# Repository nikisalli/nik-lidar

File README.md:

# nik-lidar
a low cost 3d printed 3d lidar based on ydlidar-x4, esp32 and cheap parts!

- project status: complete, needs cleanup

# info
In this repo you can find all what's necessary to assemble your own 3d lidar able to make acceptable quality 360° 3d scans

feel free to contribute since I don't have time to clean up this project

# images and results

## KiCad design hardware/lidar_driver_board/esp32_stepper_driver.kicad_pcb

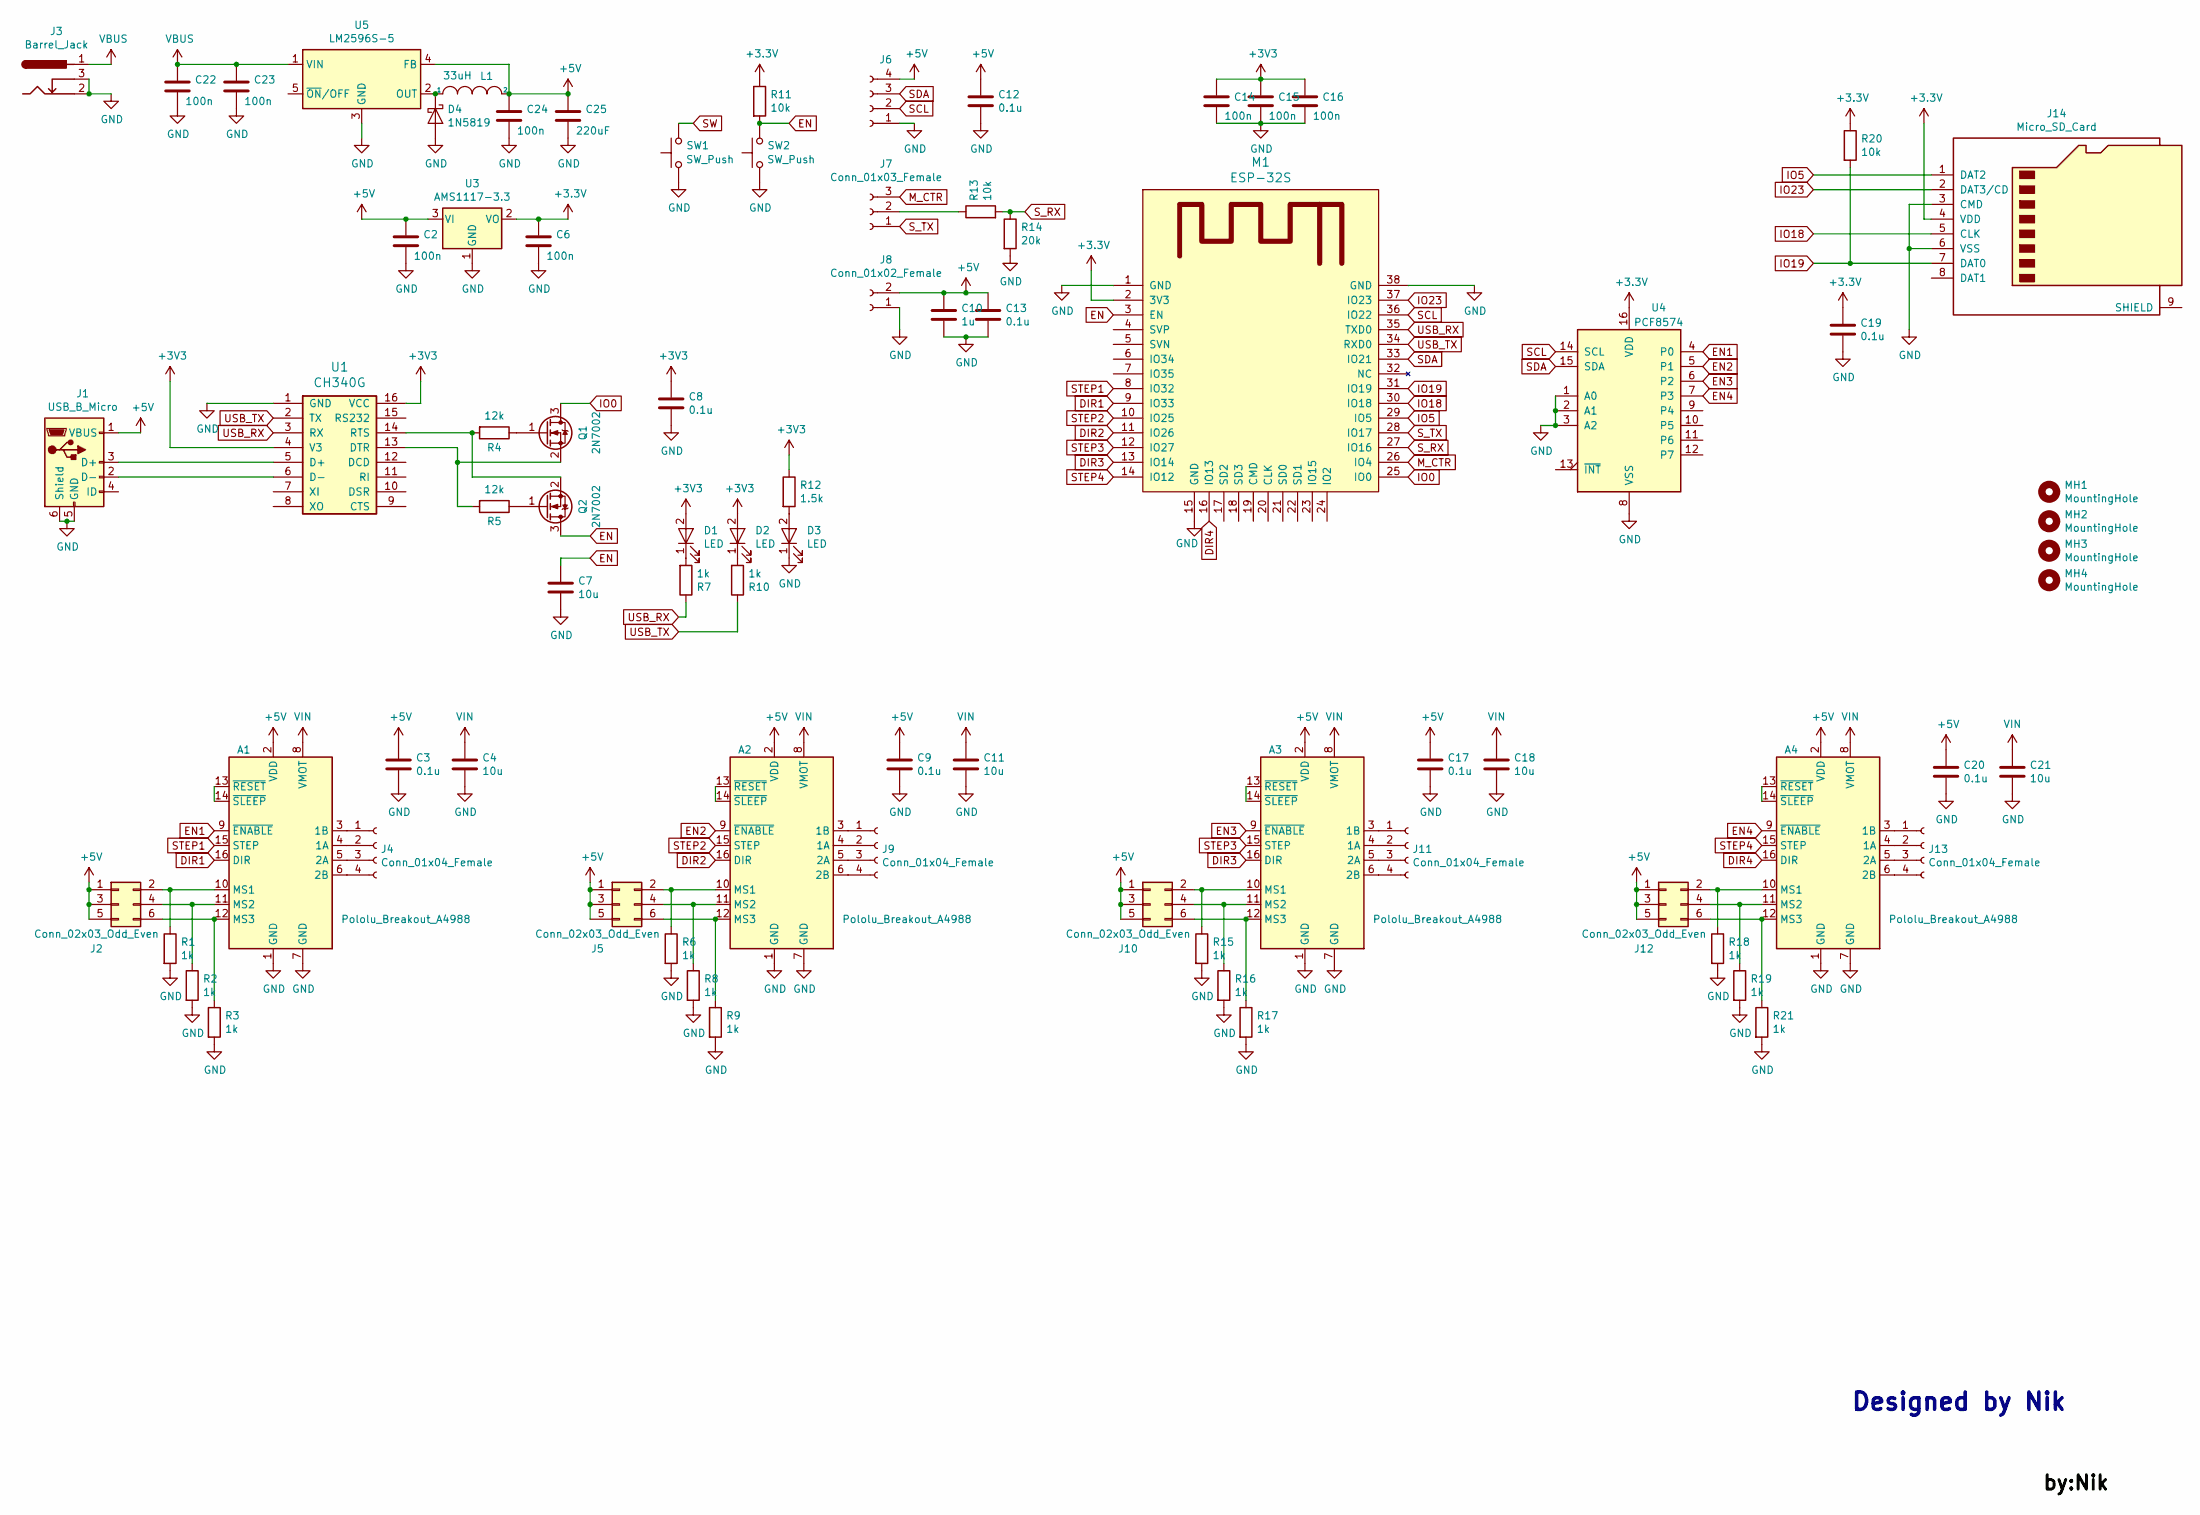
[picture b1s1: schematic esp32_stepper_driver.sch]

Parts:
A1, A2, A3, A4: Pololu_Breakout_A4988; a4988
C2, C6, C14, C15, C16, C22, C23, C24: 100n; C_0603_1608Metric
C3, C8, C9, C12, C13, C17, C19, C20: 0.1u; C_0603_1608Metric_Pad1.05x0.95mm_HandSolder
C4, C11, C18, C21: 10u; C_1206_3216Metric_Pad1.42x1.75mm_HandSolder
C7: 10u; C_1206_3216Metric
C10: 1u; C_0603_1608Metric_Pad1.05x0.95mm_HandSolder
C25: 220uF; C_Elec_6.3x7.7
D1, D2, D3: LED; LED_0603_1608Metric_Pad1.05x0.95mm_HandSolder
D4: 1N5819; D_SOD-123
J1: USB_B_Micro; USB_Micro-B_Molex_47346-0001
J2, J5, J10, J12: Conn_02x03_Odd_Even; PinHeader_2x03_P2.54mm_Vertical
J3: Barrel_Jack; BarrelJack_Horizontal
J4, J6, J9, J11, J13: Conn_01x04_Female; JST_XH_B4B-XH-A_1x04_P2.50mm_Vertical
J7: Conn_01x03_Female; JST_XH_B3B-XH-A_1x03_P2.50mm_Vertical
J8: Conn_01x02_Female; JST_XH_B2B-XH-A_1x02_P2.50mm_Vertical
J14: Micro_SD_Card; Conn_uSDcard
L1: 33uH; L_12x12mm_H8mm
M1: ESP-32S
MH1, MH2, MH3, MH4: MountingHole; MountingHole_3.2mm_M3_DIN965_Pad
Q1, Q2: 2N7002; SOT-23
R1, R2, R3, R6, R8, R9, R15, R16, R17, R18, R19, R21: 1k; R_0603_1608Metric_Pad1.05x0.95mm_HandSolder
R4, R5: 12k; R_0603_1608Metric
R7, R10: 1k; R_0603_1608Metric
R11, R13: 10k; R_0603_1608Metric
R12: 1.5k; R_0603_1608Metric
R14: 20k; R_0603_1608Metric
R20: 10k; R_0603_1608Metric_Pad1.05x0.95mm_HandSolder
SW1, SW2: SW_Push; SW_SPST_SKQG_WithoutStem
U1: CH340G; SOIC-16_3.9x9.9mm_P1.27mm
U3: AMS1117-3.3; SOT-223-3_TabPin2
U4: PCF8574; SOIC-16W_7.5x10.3mm_P1.27mm
U5: LM2596S-5; TO-263-5_TabPin3

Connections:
+5V: A1.2 (VDD), A2.2 (VDD), A3.2 (VDD), A4.2 (VDD), C2.1, C3.1, C9.1, C10.1, C12.1, C13.1, C17.1, C20.1, C24.1, C25.1, J1.1 (VBUS), J2.1, J2.3, J2.5, J5.1, J5.3, J5.5, J6.4, J8.2, J10.1, J10.3, J10.5, J12.1, J12.3, J12.5, L1.2, U3.3 (VI), U5.4 (FB)
DIR1: A1.16 (DIR), M1.9 (IO33)
DIR2: A2.16 (DIR), M1.11 (IO26)
DIR3: A3.16 (DIR), M1.13 (IO14)
DIR4: A4.16 (DIR), M1.16 (IO13)
EN: C7.1, M1.3 (EN), Q2.3 (D), R11.2, SW2.2
EN1: A1.9 (~ENABLE), U4.4 (P0)
EN2: A2.9 (~ENABLE), U4.5 (P1)
EN3: A3.9 (~ENABLE), U4.6 (P2)
EN4: A4.9 (~ENABLE), U4.7 (P3)
GND: A1.1 (GND), A1.7 (GND), A2.1 (GND), A2.7 (GND), A3.1 (GND), A3.7 (GND), A4.1 (GND), A4.7 (GND), C2.2, C3.2, C4.2, C6.2, C7.2, C8.2, C9.2, C10.2, C11.2, C12.2, C13.2, C14.2, C15.2, C16.2, C17.2, C18.2, C19.2, C20.2, C21.2, C22.2, C23.2, C24.2, C25.2, D3.1 (K), D4.2 (A), J1.5 (GND), J1.6 (Shield), J3.2, J3.3, J6.1, J8.1, J14.3 (CMD), J14.6 (VSS), M1.1 (GND), M1.15 (GND), M1.38 (GND), R1.2, R2.2, R3.2, R6.2, R8.2, R9.2, R14.2, R15.2, R16.2, R17.2, R18.2, R19.2, R21.2, SW1.1, SW2.1, U1.1 (GND), U3.1 (GND), U4.1 (A0), U4.2 (A1), U4.3 (A2), U4.8 (VSS), U5.3 (GND)
IO0: M1.25 (IO0), Q1.3 (D)
IO5: J14.1 (DAT2), M1.29 (IO5)
IO18: J14.5 (CLK), M1.30 (IO18)
IO19: J14.7 (DAT0), M1.31 (IO19), R20.2
IO23: J14.2 (DAT3/CD), M1.37 (IO23)
M_CTR: J7.3, M1.26 (IO4)
unnamed: A1.3 (1B), J4.1
unnamed: A1.4 (1A), J4.2
unnamed: A1.5 (2A), J4.3
unnamed: A1.6 (2B), J4.4
unnamed: A1.10 (MS1), J2.2, R1.1
unnamed: A1.11 (MS2), J2.4, R2.1
unnamed: A1.12 (MS3), J2.6, R3.1
unnamed: A1.13 (~RESET), A1.14 (~SLEEP)
unnamed: A2.3 (1B), J9.1
unnamed: A2.4 (1A), J9.2
unnamed: A2.5 (2A), J9.3
unnamed: A2.6 (2B), J9.4
unnamed: A2.10 (MS1), J5.2, R6.1
unnamed: A2.11 (MS2), J5.4, R8.1
unnamed: A2.12 (MS3), J5.6, R9.1
unnamed: A2.13 (~RESET), A2.14 (~SLEEP)
unnamed: A3.3 (1B), J11.1
unnamed: A3.4 (1A), J11.2
unnamed: A3.5 (2A), J11.3
unnamed: A3.6 (2B), J11.4
unnamed: A3.10 (MS1), J10.2, R15.1
unnamed: A3.11 (MS2), J10.4, R16.1
unnamed: A3.12 (MS3), J10.6, R17.1
unnamed: A3.13 (~RESET), A3.14 (~SLEEP)
unnamed: A4.3 (1B), J13.1
unnamed: A4.4 (1A), J13.2
unnamed: A4.5 (2A), J13.3
unnamed: A4.6 (2B), J13.4
unnamed: A4.10 (MS1), J12.2, R18.1
unnamed: A4.11 (MS2), J12.4, R19.1
unnamed: A4.12 (MS3), J12.6, R21.1
unnamed: A4.13 (~RESET), A4.14 (~SLEEP)
unnamed: D1.1 (K), R7.2
unnamed: D2.1 (K), R10.2
unnamed: D3.2 (A), R12.2
unnamed: D4.1 (K), L1.1, U5.2 (OUT)
unnamed: J1.2 (D-), U1.6 (D-)
unnamed: J1.3 (D+), U1.5 (D+)
unnamed: J7.2, R13.1
unnamed: Q1.1 (G), R4.1
unnamed: Q1.2 (S), R5.2, U1.13 (DTR)
unnamed: Q2.1 (G), R5.1
unnamed: Q2.2 (S), R4.2, U1.14 (RTS)
SCL: J6.2, M1.36 (IO22), U4.14 (SCL)
SDA: J6.3, M1.33 (IO21), U4.15 (SDA)
STEP1: A1.15 (STEP), M1.8 (IO32)
STEP2: A2.15 (STEP), M1.10 (IO25)
STEP3: A3.15 (STEP), M1.12 (IO27)
STEP4: A4.15 (STEP), M1.14 (IO12)
SW: SW1.2
S_RX: M1.27 (IO16), R13.2, R14.1
S_TX: J7.1, M1.28 (IO17)
USB_RX: M1.35 (TXD0), R7.1, U1.3 (RX)
USB_TX: M1.34 (RXD0), R10.1, U1.2 (TX)
VBUS: C22.1, C23.1, J3.1, U5.1 (VIN)
VIN: A1.8 (VMOT), A2.8 (VMOT), A3.8 (VMOT), A4.8 (VMOT), C4.1, C11.1, C18.1, C21.1

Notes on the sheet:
Designed by Nik

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
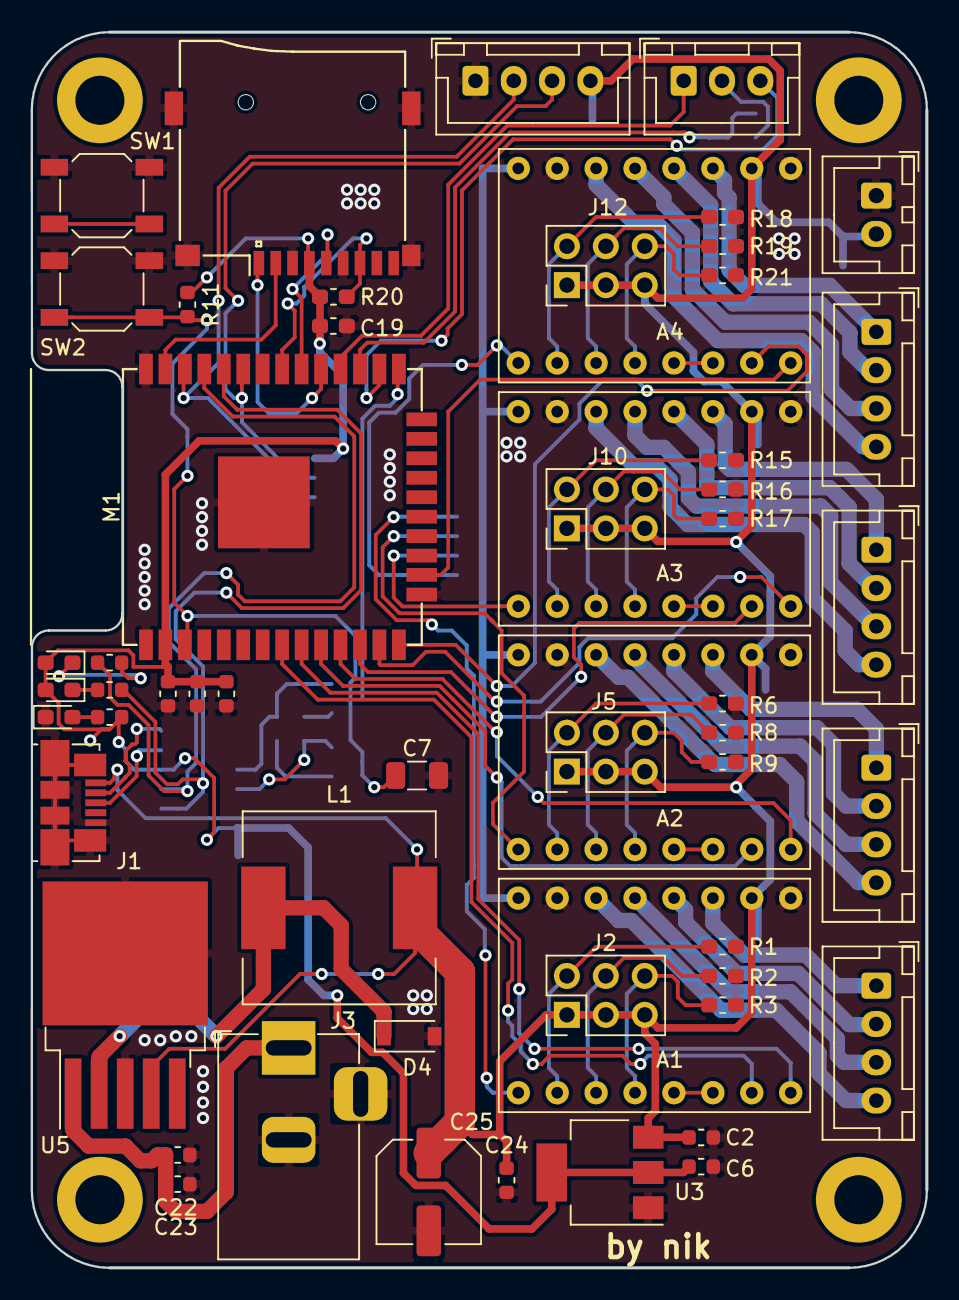
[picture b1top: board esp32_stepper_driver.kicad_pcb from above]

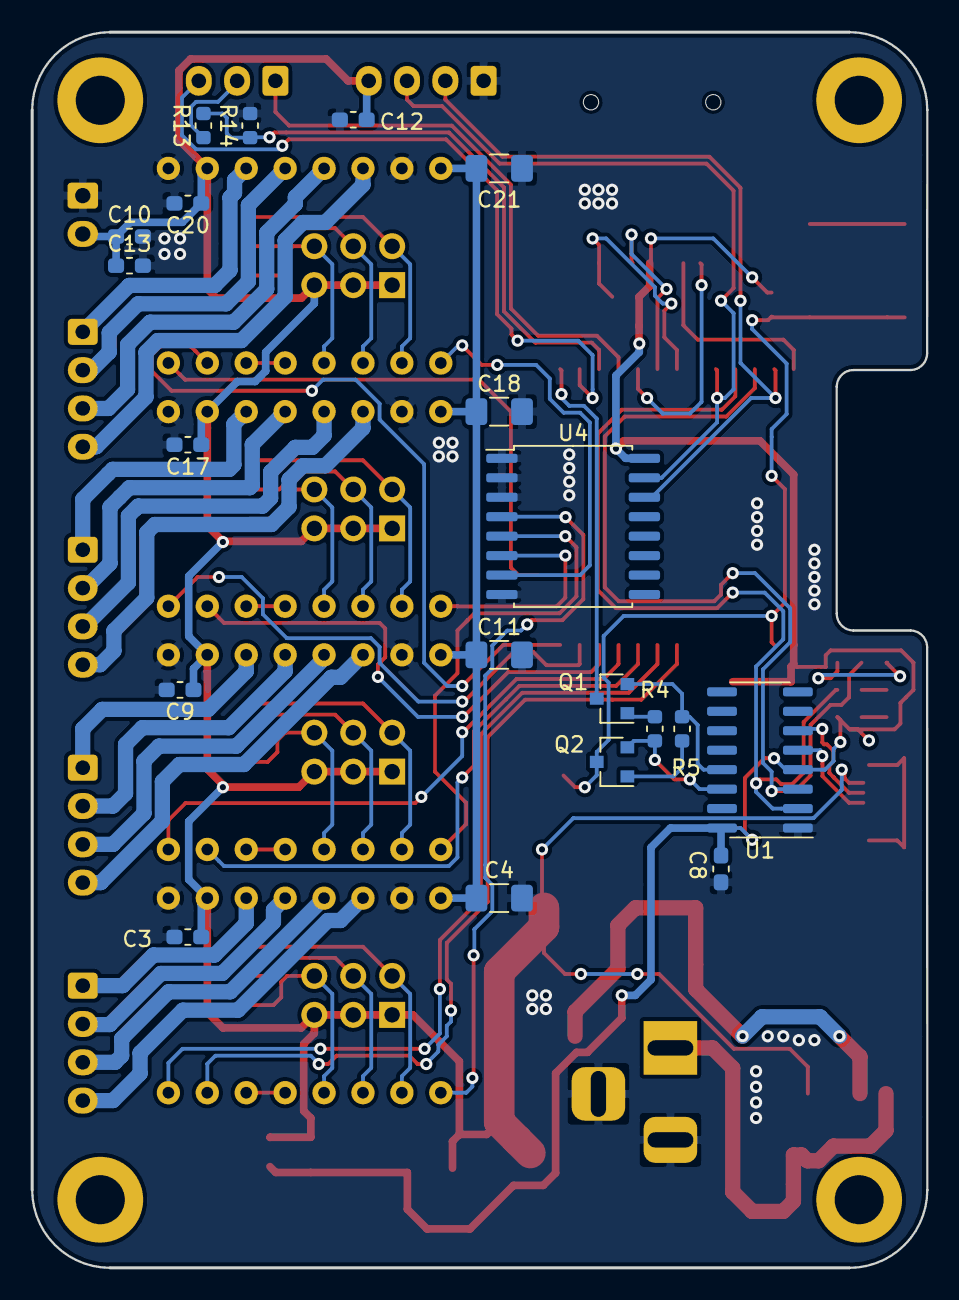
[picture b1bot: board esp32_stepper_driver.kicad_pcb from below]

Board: 2 copper layers, 58.4 x 80.6 mm, 80 parts (20 on the bottom side), 73 nets.

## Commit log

2020-05-03 added ota upload and basic motor setup
2020-05-09 first working build
2020-05-11 fixed some things
2020-07-16 added example config file, 3d files and fixed bugs
2020-07-21 changed file names and added pcb and schematics
2021-03-23 hardware fixes
2021-03-23 added images
2021-03-23 added images to readme
2021-03-23 fixed file name
2021-04-09 better scan client
2021-04-10 minor fix
2021-04-10 added manual mode if autoscan
2021-04-10 manual mode fix
2021-04-10 better timeout method
2021-04-10 added auto - manual mode
2021-04-10 fixed bug
